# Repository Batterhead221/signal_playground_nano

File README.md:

# signal_playground_nano
A compact CR2032-powered RGB LED learning board with tactile switches, brightness boost, and playful silkscreen art.

# Signal Playground Nano

A compact CR2032-powered RGB LED learning PCB made for Madeline.

This board demonstrates simple electronics concepts through a playful, hands-on layout:

- Common-anode RGB LED wiring
- Current-limiting resistors
- Momentary switch control
- Global brightness boost
- Coin-cell power
- Cute silkscreen art for a kid-friendly learning board

## Features

- CR2032 battery powered
- RGB LED with individual red, green, and blue buttons
- BRIGHT button that bypasses a series dimming resistor
- Compact rounded PCB
- Kid-friendly silkscreen labels and artwork

## Revision

Current hardware revision:

Signal Playground Nano Rev A

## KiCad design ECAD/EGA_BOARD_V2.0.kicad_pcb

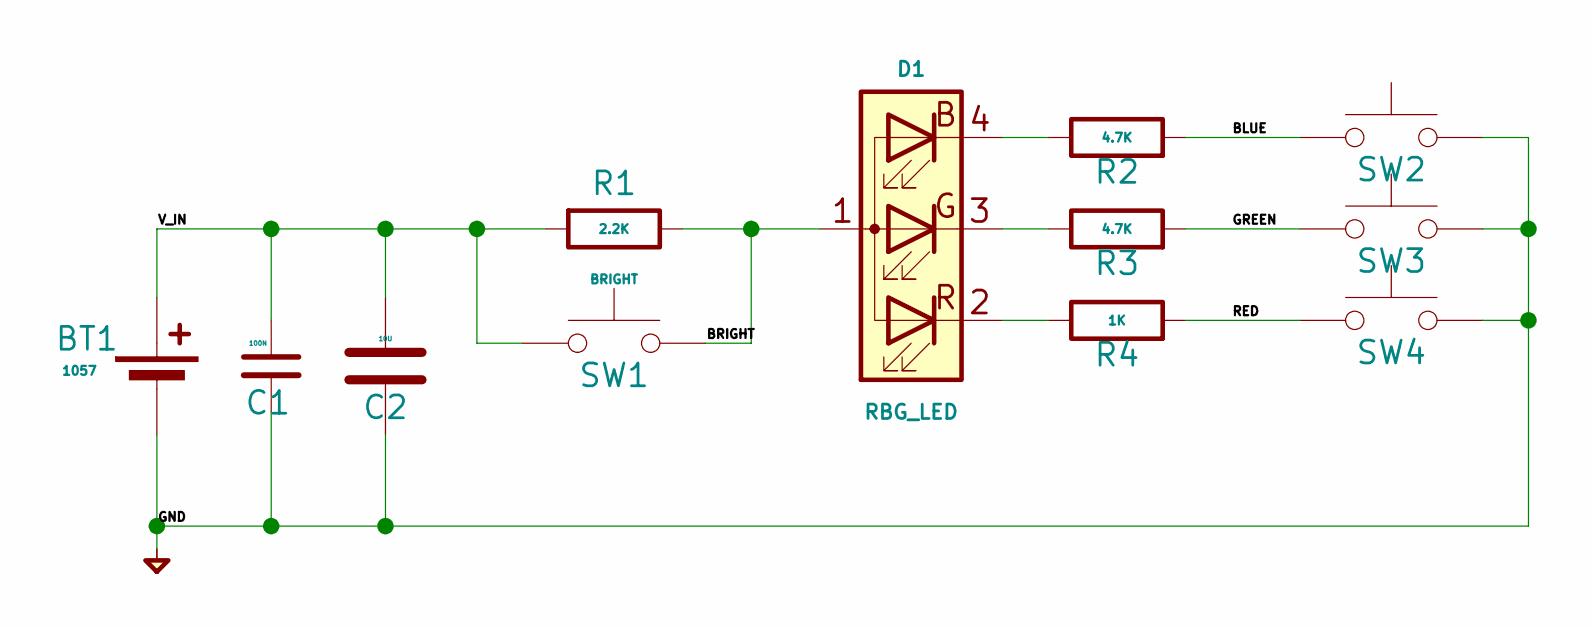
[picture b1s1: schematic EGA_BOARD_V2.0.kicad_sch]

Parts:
BT1: 1057; BAT_1057
C1: 100N; C_0603_1608Metric
C2: 10U; C_0805_2012Metric
D1: RBG_LED; LED_Cree-PLCC4_3.2x2.8mm_CCW
R1: 2.2K; C_0603_1608Metric
R2, R3: 4.7K; C_0603_1608Metric
R4: 1K; C_0603_1608Metric
SW1: BRIGHT; SW_SPST_Omron_B3FS-100xP
SW2, SW3, SW4: SWITCH (B3F-1020); SW_TH_Tactile_Omron_B3F-102x

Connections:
/BLUE: R2.2, SW2.1
/BRIGHT: D1.1 (A), R1.1, SW1.2
/GREEN: R3.2, SW3.1
/RED: R4.2, SW4.1
/V_IN: BT1.1 (+), C1.1, C2.1, R1.2, SW1.1
GND: BT1.2 (-_2), C1.2, C2.2, SW2.2, SW3.2, SW4.2
unnamed: D1.4 (BK), R2.1
unnamed: D1.3 (GK), R3.1
unnamed: D1.2 (RK), R4.1

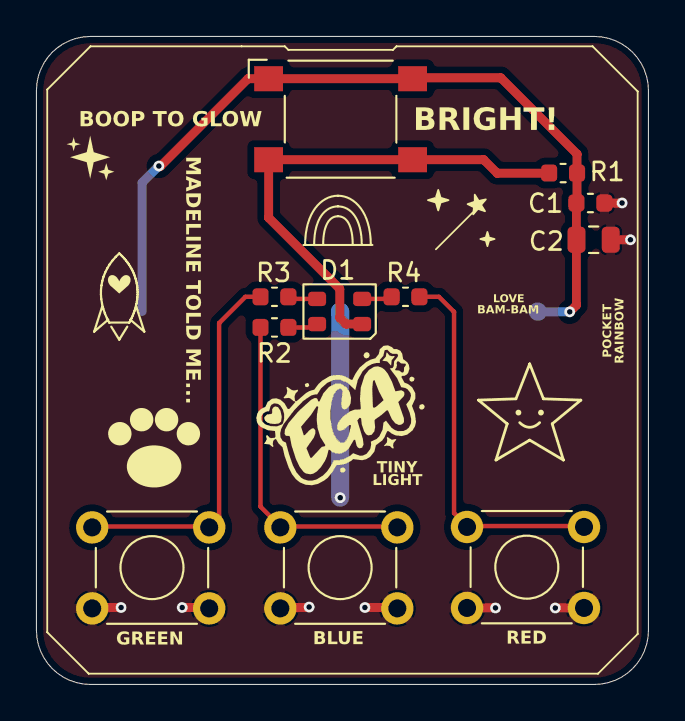
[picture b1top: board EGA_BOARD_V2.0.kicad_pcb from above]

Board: 2 copper layers, 34.0 x 36.0 mm, 12 parts (1 on the bottom side), 9 nets.

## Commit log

2026-05-07 V2 of EGA board or SIG_PLAYGND
2026-05-13 Revised repo
